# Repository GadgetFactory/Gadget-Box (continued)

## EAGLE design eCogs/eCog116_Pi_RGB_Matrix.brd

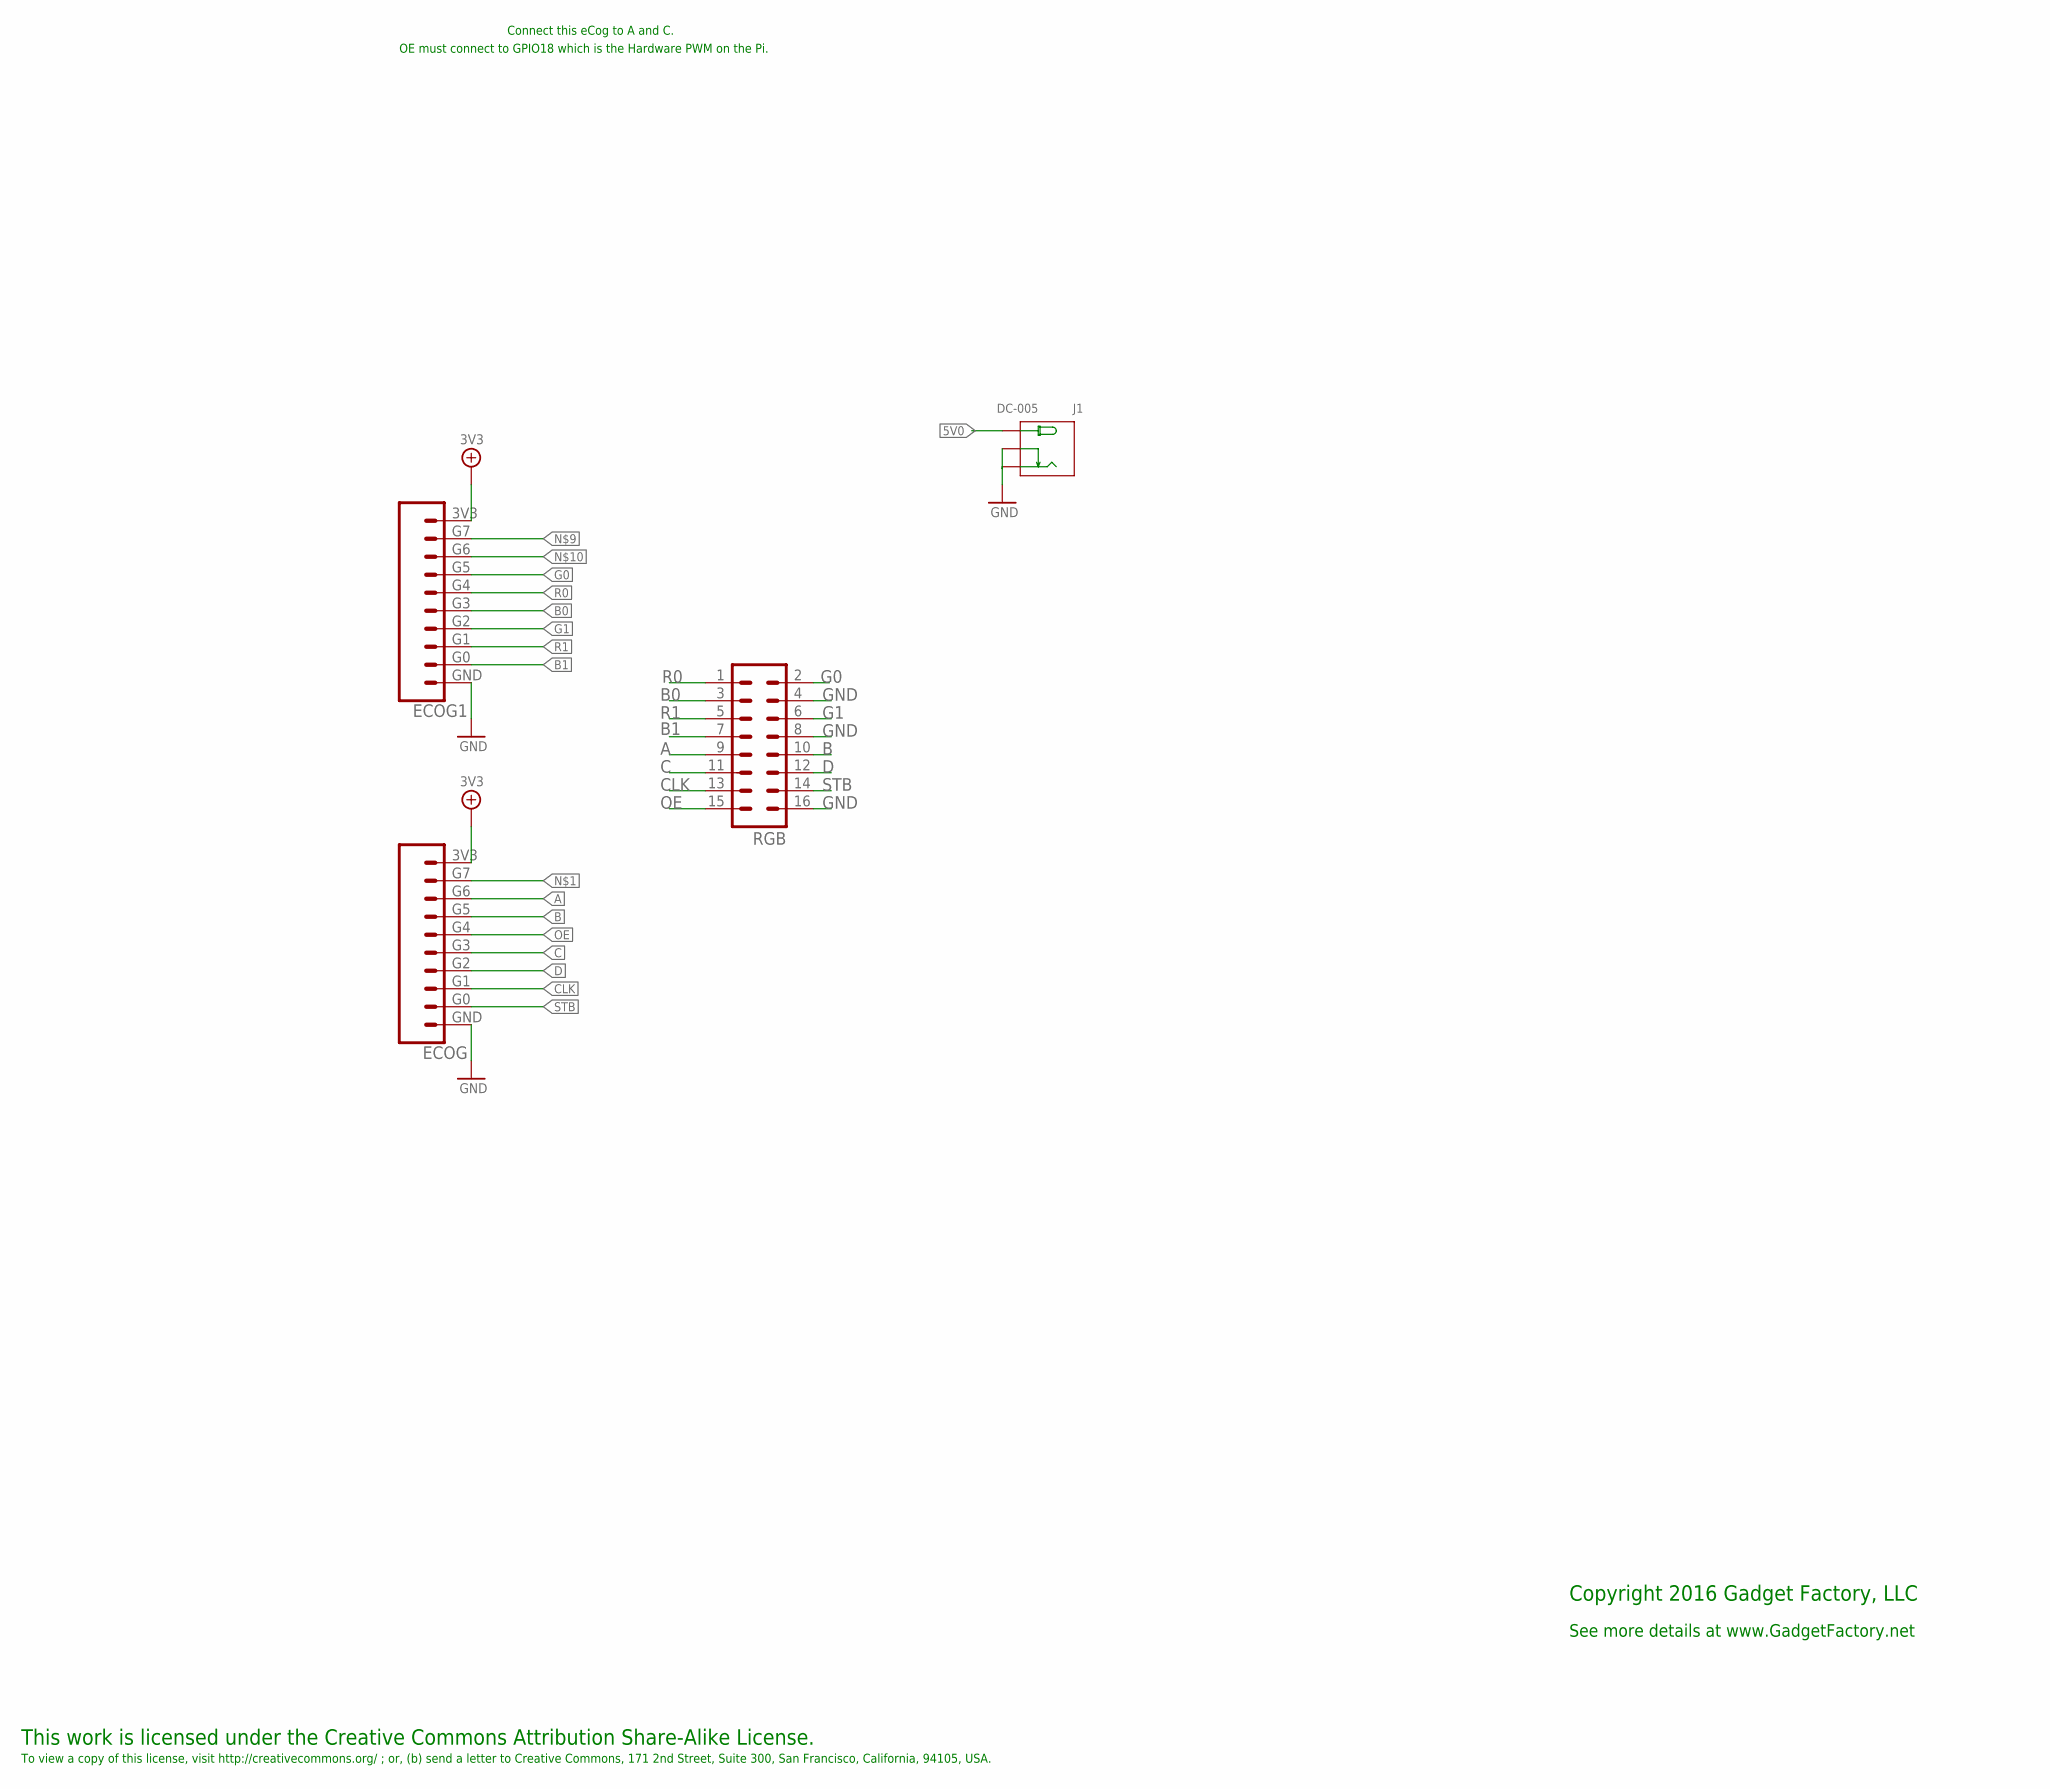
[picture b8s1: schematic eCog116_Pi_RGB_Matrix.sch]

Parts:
ECOG, ECOG1: ECOG_GENERAL_ROWTHROUGHOLE; ECOG_GENERAL_TH
J1: DC-005; DCJ3P-14.2X11.0X9.0MM
RGB: ML16; PARTNO PRPC004DAAN-RC

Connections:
3V3: ECOG.3V3, ECOG1.3V3
5V0: J1.+
A: ECOG.G6, RGB.9
B: ECOG.G5, RGB.10
B0: ECOG1.G3, RGB.3
B1: ECOG1.G0, RGB.7
C: ECOG.G3, RGB.11
CLK: ECOG.G1, RGB.13
D: ECOG.G2, RGB.12
G0: ECOG1.G5, RGB.2
G1: ECOG1.G2, RGB.6
GND: ECOG.GND, ECOG1.GND, J1.-1 (-), J1.-2 (CDN), RGB.4, RGB.8, RGB.16
OE: ECOG.G4, RGB.15
R0: ECOG1.G4, RGB.1
R1: ECOG1.G1, RGB.5
STB: ECOG.G0, RGB.14

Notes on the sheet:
This work is licensed under the Creative Commons Attribution Share-Alike License.
To view a copy of this license, visit http://creativecommons.org/ ; or, (b) send a letter to Creative Commons, 171 2nd Street, Suite 300, San Francisco, California, 94105, USA.
Copyright 2016 Gadget Factory, LLC
See more details at www.GadgetFactory.net
Connect this eCog to A and C.
OE must connect to GPIO18 which is the Hardware PWM on the Pi.

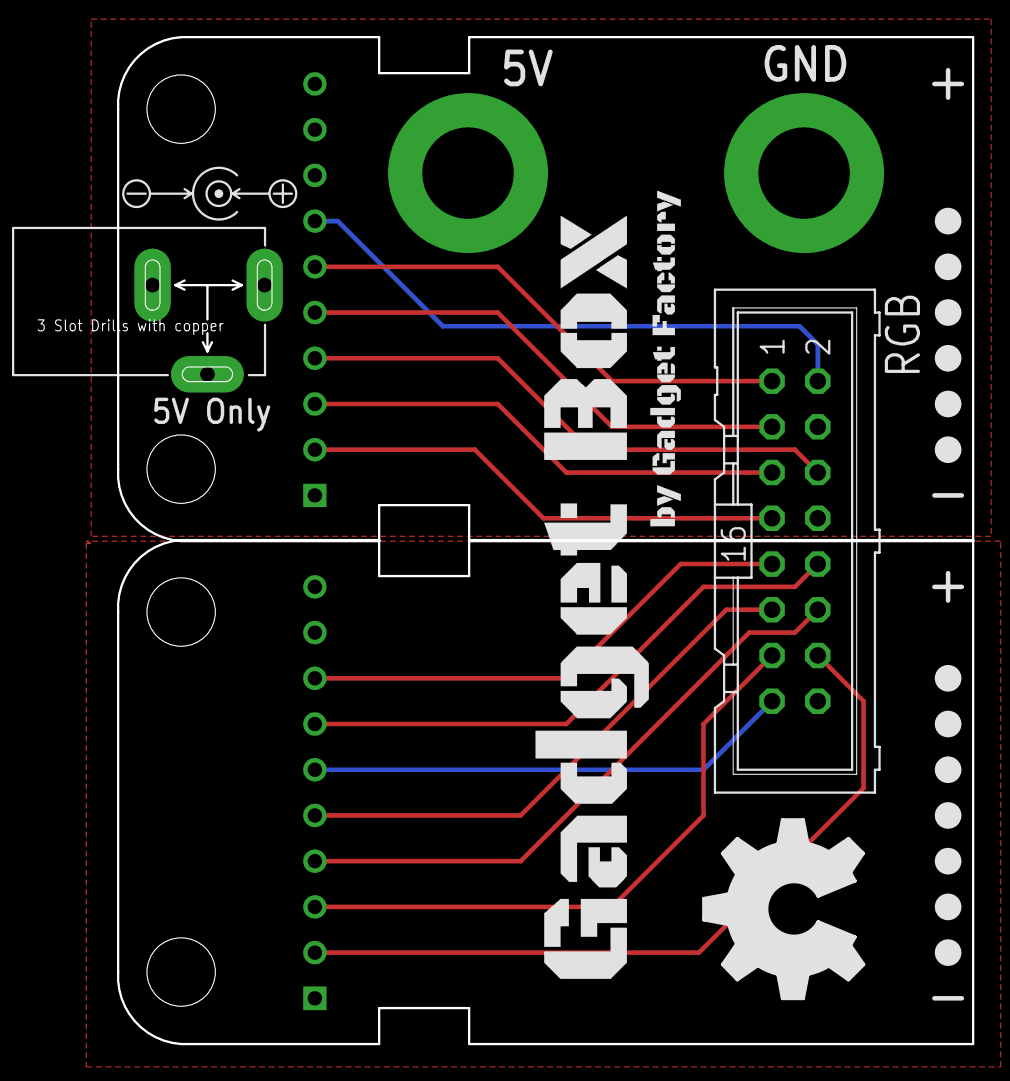
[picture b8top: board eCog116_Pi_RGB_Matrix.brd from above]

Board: 2 copper layers, 52.0 x 55.9 mm, 19 parts (0 on the bottom side), 15 nets.

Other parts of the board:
U$1: GADGETBOX_TEXT
U$2, U$3, U$4, U$5, U$6, U$7, U$8, U$9, U$11, U$12, U$13, U$14, U$15: LEGEND_DIO
U$10: OSHW_FILLX350_NOTEXT

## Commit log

2016-03-25 :tada: Added .gitattributes & .gitignore files
2016-03-25 Gadget-Box Derived from Firefly-Box
2016-03-28 Change the spacings to fit enclosure and headers to eCogs.
2016-03-28 Update library and templates for surface mount pin headers.
2016-03-28 Update pin names for the buses
2016-04-21 V1.1
2016-04-22 New eCogs
2016-06-27 Exclusions
2016-06-27 Latest updated to V1.4
2016-06-28 Updated the legend on the silkscreen
2016-06-29 Added "To get started" to bottom silkscreen
2016-06-29 Remote Control eCog
2016-06-29 Thumb Slide eCog
2016-06-29 Added parts to attributes for BOM
2016-06-29 Added Box text to silkscreen
2016-06-29 Moved templates into folder
2016-06-29 made the first panel of eCogs
2016-06-30 A couple more eCog panels
2016-06-30 Update all of the Fonts and graphics
2016-06-30 ignore files
2016-06-30 Fix a trace on the Sensor eCog that went through cutout.
2016-07-06 Version 1.6 - Changed Crystal to 8Mhz and 16Mhz footprint.
    Updated silkscreen
2016-07-06 GadgetBox - Version 1.7
    7/6/2016 V1.6 GadgetBox
    Changed size of board to fit white cases. 93.5x53.5
    Added voltage divider to allow capturing battery power on pin D5.
    Added all BOM info.
    Rerouted 3.3v and GND to provide better paths.
    Moved location of compontents for the BH silkscreen and the new board
2016-07-11 Added new eCogs
2016-07-11 GadgetBox V1.7
2016-07-11 GadgetBox V1.7
    Move the On/Off locations
2016-08-10 revision 1.0
2016-08-10 GB Mini Pro V1.2
2016-08-10 Fixed the backwards rx and tx lines.
2016-08-10 Update Silkscreen
2016-08-10 V1.2
    Moved JST battery connector
2016-08-10 V1.2.1
    Fixed a problem with A0-A3
2016-08-16 All the 2.0 updates
2016-09-29 Reorganized
2016-09-29 cleanup
2016-09-29 Changed the pins to support PWM in correct locations
2016-09-29 Moved pi zero over 2mm to make room for SD card.
2016-09-30 Removed all charging circuits.
2016-09-30 Fixed silkscreen
2016-09-30 Updated silkscreen
2016-09-30 Add a second, cheaper crystal option.
2016-09-30 Fixed problem with silkscreen
2016-09-30 Add resistor to prevent 3.3V from FTDI Module.
2016-10-03 Added BOM info
2016-10-03 Updated silkscreen and BOM for GadgetBox-ESP8266
2016-10-03 Redid the Mini Pro Clone with better routing.
2016-10-03 Added a new version that only uses modules.
2016-10-04 Removed BAT from silkscreen
2016-10-05 Updated Li-ON module and moved battery connector to top.
2016-10-06 Get rid of the 5V and RST on separate headers.
2016-10-06 Removed RST and 5V - Fixed silkscreen
2016-10-06 Fixed charging circuit
2016-10-06 Added battery cable cutout
2016-10-06 Fixed Silkscreen - Pizero
2016-10-06 Changed Version text - Mini Pro
2016-10-06 Not ready - needs a 3.3V power supply.
2016-10-06 Added charging circuit.
2016-10-07 Add battery wire cutout.
2016-10-12 Cleanup eCogs library
2016-10-12 Update Remote Control Design
    Put the transmit PWM pin on XC4 for greater compatibility.
2016-10-12 Updated to latest eCog Library
2016-10-12 Redid P101
    Using Through hole and different arrangement
2016-10-12 Changed the USB connector per Seeed request.
2016-10-12 Flipped the sensor around to fit in boxes with modules in the middle.
2016-10-12 pCog for Sensor Version 1.1
2016-10-12 Added + and - to silkscreen for display eCog
2016-10-12 Fix silkscreen
2016-10-13 Added Dual row footprint
2016-10-13 Added 5V Template
2016-10-13 New NodeMCU Motherboard
2016-10-13 Moved battery connector
2016-10-13 PS2 Keyboard eCog
2016-10-14 Pi RGB Matrix eCog
2016-10-14 pCog103 for Barcode Genie
2016-10-17 First cut at Arduino support library.
2016-10-18 Working IRBox example
2016-10-27 Fix some text
2016-10-27 Laundry Minder example
2016-10-27 Update defaults
2016-10-27 Move Files
2016-10-27 Remove extra files
2016-10-27 Update License info
2016-10-28 Move hardware to another Git, this is for the Arduino Library now.
2016-10-28 Arduino 1.5 library format
2016-12-05 Cleanup and update the examples.
2016-12-05 Changes to make everything fit in Arduino Mini Pro
2016-12-06 Update to work with NodeMCU
2016-12-06 Fix ESP8266 pins.
2016-12-06 New release with NodeMCU pin fix
2016-12-06 Clean
2016-12-07 Better detection of board types.
2016-12-16 Update Universal remote with Terminal
2016-12-16 Move credentials to its own location
2016-12-16 Added OLED display
2016-12-19 Continuous IR Receive.
2016-12-19 Print name of IR signal.
2016-12-19 Cleanup some comments.
2016-12-19 SmartConfig without Blynk token.
2016-12-19 WifiManager and OTA updates added for esp8266
2016-12-20 Moved all WifiManager and OTA stuff out of main .ino file.
2016-12-20 Handle the Blynk restart bug.
2016-12-20 Disable Blynk debugging for Mini Pro.
2016-12-20 Better way to handle Blynk debugging, Teensy and NodeMCU have plenty of room.
2016-12-30 Fix for pin locations.
2017-01-10 eCog examples
2017-01-13 more eCog examples
2017-04-09 eCog106 demo (Button Only)
    eCog106 demo (Button Only)
2017-04-09 Update and rename eCog106-Button-and-LED.ino to eCog106-Button-and-Serial.ino
    renamed file. added a comment
2017-04-09 Create eCog106-Button-and-LED.ino
    eCog106-Button-and-LED Example..
    -- Holding Button 3 makes LED 4 blink fast
    -- Holding Button 2 makes LED 1 mimic the Arduino LED
2017-04-09 Update eCog106-Button-and-Serial.ino
    annotated that Arduino Mini Pro A6/A7 are usable only for analogRead (CC1 CC2 DC1 DC2 pins of C and D eCog slots)
2017-04-09 typo fix
